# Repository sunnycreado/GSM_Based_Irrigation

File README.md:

# GSM_Based_Irrigation
GSM_Based_Irrigation

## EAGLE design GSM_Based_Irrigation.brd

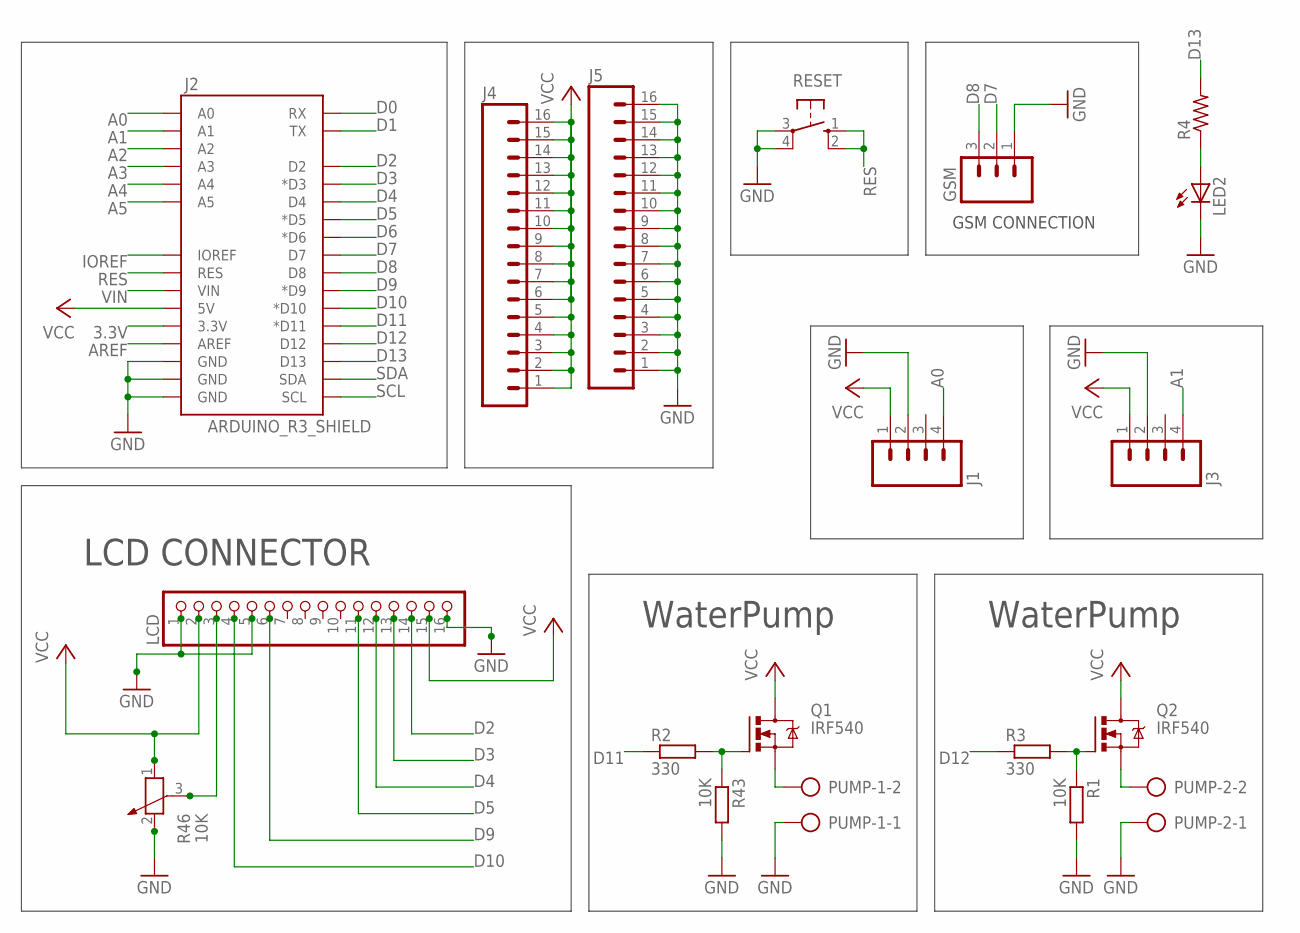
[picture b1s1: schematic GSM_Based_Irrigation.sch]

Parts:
GSM: M03LONGPADS; 1X03_LONGPADS
J1, J3: M04LONGPADS; 1X04_LONGPADS
J2: ARDUINO_R3_SHIELD; UNO_R3_SHIELD
J4, J5: M16LONGPADS; 1X16_LONGPADS
LCD: PINHD-1X16; 1X16
LED2: LED5MM
PUMP-1, PUMP-2: AK300/2
Q1, Q2: IRF540; TO220BV
R1, R43: 10K; 0207/7@1
R2, R3: 330; 0207/7@1
R4: R-US_0207/10; 0207/10
R46: 10K; PT-10
RESET: 10-XX; B3F-10XX

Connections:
3.3V: J2.3.3V
A0: J1.4, J2.A0
A1: J2.A1, J3.4
A2: J2.A2
A3: J2.A3
A4: J2.A4
A5: J2.A5
AREF: J2.AREF
D0: J2.RX
D1: J2.TX
D2: J2.D2, LCD.14
D3: J2.D3 (*D3), LCD.13
D4: J2.D4, LCD.12
D5: J2.D5 (*D5), LCD.11
D6: J2.D6 (*D6)
D7: GSM.2, J2.D7
D8: GSM.3, J2.D8
D9: J2.D9 (*D9), LCD.6
D10: J2.D10 (*D10), LCD.4
D11: J2.D11 (*D11), R2.1
D12: J2.D12, R3.1
D13: J2.D13, R4.2
GND: GSM.1, J1.2, J2.GND@0 (GND), J2.GND@1 (GND), J2.GND@2 (GND), J3.2, J5.1, J5.2, J5.3, J5.4, J5.5, J5.6, J5.7, J5.8, J5.9, J5.10, J5.11, J5.12, J5.13, J5.14, J5.15, J5.16, LCD.1, LCD.5, LCD.16, LED2.K (C), PUMP-1.1, PUMP-2.1, R1.2, R43.2, R46.2, RESET.3, RESET.4 (P1)
IOREF: J2.IOREF
unnamed: PUMP-1.2, Q1.S
unnamed: PUMP-2.2, Q2.S
unnamed: Q1.G, R2.2, R43.1
unnamed: LED2.A, R4.1
unnamed: Q2.G, R1.1, R3.2
unnamed: LCD.3, R46.3
RES: J2.RES, RESET.1 (S), RESET.2 (S1)
SCL: J2.SCL
SDA: J2.SDA
VCC: J1.1, J2.5V, J3.1, J4.1, J4.2, J4.3, J4.4, J4.5, J4.6, J4.7, J4.8, J4.9, J4.10, J4.11, J4.12, J4.13, J4.14, J4.15, J4.16, LCD.2, LCD.15, Q1.D, Q2.D, R46.1
VIN: J2.VIN

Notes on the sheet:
WaterPump
LCD CONNECTOR
GSM CONNECTION

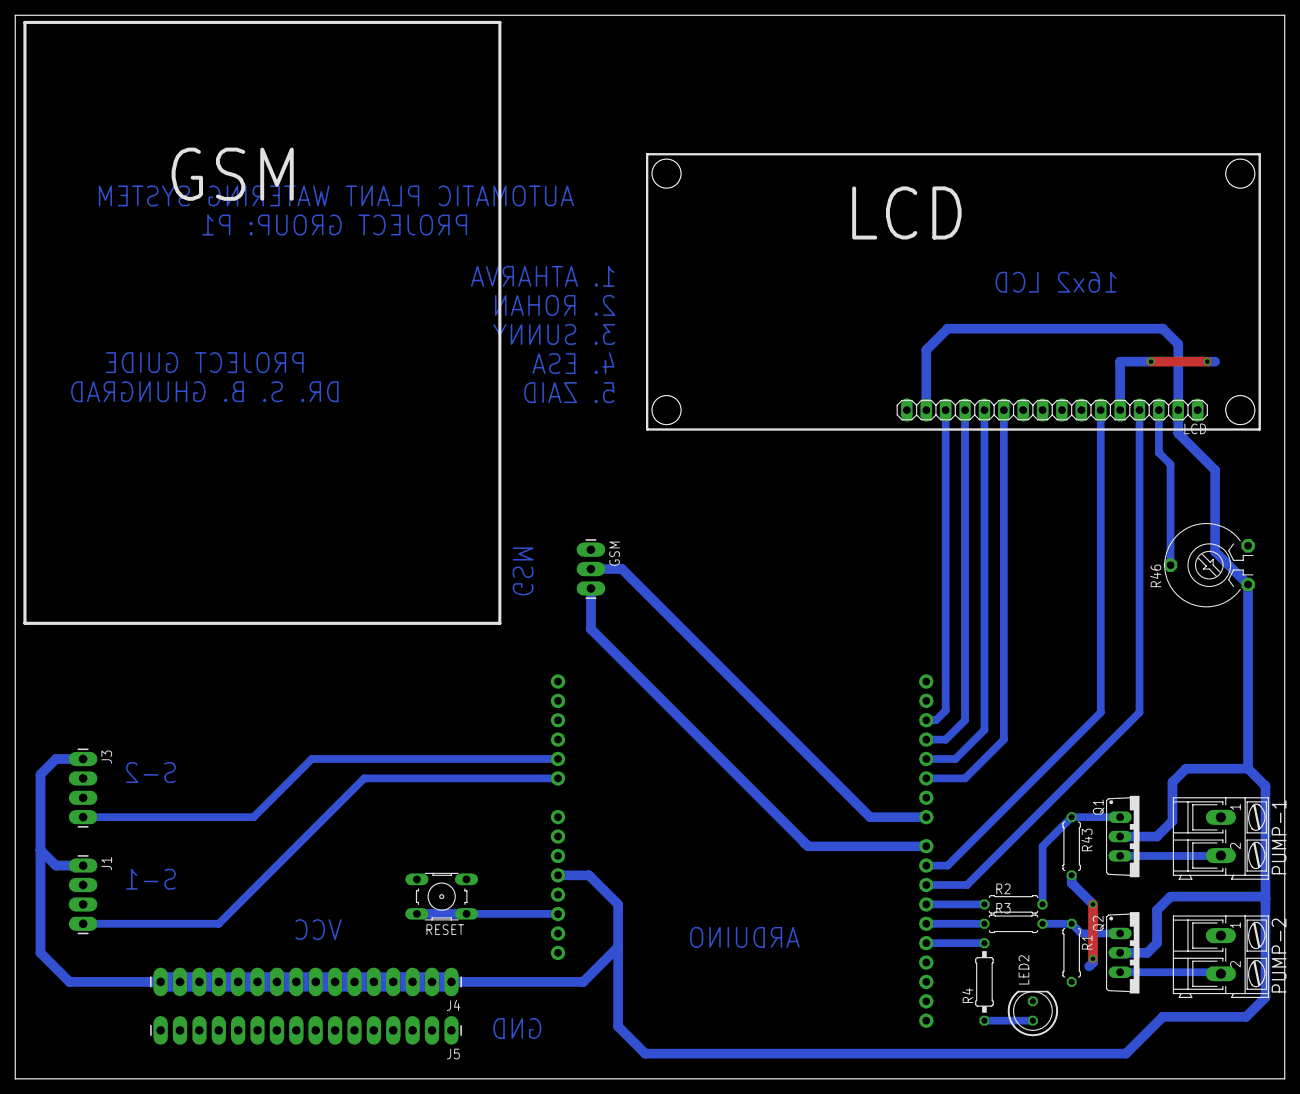
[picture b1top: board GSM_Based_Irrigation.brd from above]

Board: 2 copper layers, 166.3 x 139.4 mm, 19 parts (1 on the bottom side), 22 nets.

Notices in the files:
parts and their libraries:
SparkFun-Boards: Licensing: Creative Commons ShareAlike 4.0 International - https://creativecommons.org/licenses/by-sa/4.0
SparkFun-Aesthetics: Licensing: CC v3.0 Share-Alike You are welcome to use this library for commercial purposes.
